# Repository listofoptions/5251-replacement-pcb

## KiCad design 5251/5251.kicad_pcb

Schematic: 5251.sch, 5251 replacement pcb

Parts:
J1: Conn_01x30; BEAMSPRING-CARD-EDGE
U1: F1_SENSE; SENSE_PAD
U2: F1; BEAMSPRING_PAD
U3: F2; BEAMSPRING_PAD
U4: RIGHT_TAB_SENSE; SENSE_PAD
U5: TILDE; BEAMSPRING_PAD
U6: 1; BEAMSPRING_PAD
U7: 2; BEAMSPRING_PAD
U8: 3; BEAMSPRING_PAD
U9: 4; BEAMSPRING_PAD
U10: 5; BEAMSPRING_PAD
U11: 6; BEAMSPRING_PAD
U12: 7; BEAMSPRING_PAD
U13: 8; BEAMSPRING_PAD
U14: 9; BEAMSPRING_PAD
U15: 0; BEAMSPRING_PAD
U16: -_; BEAMSPRING_PAD
U17: =+; BEAMSPRING_PAD
U18: BACKSPACE; BEAMSPRING_PAD
U19: PAD7; BEAMSPRING_PAD
U20: LEFT_TAB; BEAMSPRING_PAD
U21: PAD9; BEAMSPRING_PAD
U22: DUP; BEAMSPRING_PAD
U23: F3_SENSE; SENSE_PAD
U24: F3; BEAMSPRING_PAD
U25: F4; BEAMSPRING_PAD
U26: F9; BEAMSPRING_PAD
U27: CONTROL; BEAMSPRING_PAD
U28: RIGHT_TAB; BEAMSPRING_PAD
U29: Q; BEAMSPRING_PAD
U30: W; BEAMSPRING_PAD
U31: E; BEAMSPRING_PAD
U32: R; BEAMSPRING_PAD
U33: T; BEAMSPRING_PAD
U34: Y; BEAMSPRING_PAD
U35: U; BEAMSPRING_PAD
U36: I; BEAMSPRING_PAD
U37: O; BEAMSPRING_PAD
U38: P; BEAMSPRING_PAD
U39: BANG-CENT; BEAMSPRING_PAD
U40: \\|; BEAMSPRING_PAD
U41: FIELD_EXIT; BEAMSPRING_PAD
U42: PAD4; BEAMSPRING_PAD
U43: PAD8; BEAMSPRING_PAD
U44: PAD6; BEAMSPRING_PAD
U45: FIELD-; BEAMSPRING_PAD
U46: F5_SENSE; SENSE_PAD
U47: F5; BEAMSPRING_PAD
U48: F6; BEAMSPRING_PAD
U49: F9_SENSE; SENSE_PAD
U50: LEFT_SHIFT; BEAMSPRING_PAD
U51: <>; BEAMSPRING_PAD
U52: A; BEAMSPRING_PAD
U53: S; BEAMSPRING_PAD
U54: D; BEAMSPRING_PAD
U55: F; BEAMSPRING_PAD
U56: G; BEAMSPRING_PAD
U57: H; BEAMSPRING_PAD
U58: J; BEAMSPRING_PAD
U59: K; BEAMSPRING_PAD
U60: L; BEAMSPRING_PAD
U61: ;; BEAMSPRING_PAD
U62: '; BEAMSPRING_PAD
U63: {}; BEAMSPRING_PAD
U64: RETURN; BEAMSPRING_PAD
U65: PAD1; BEAMSPRING_PAD
U66: PAD5; BEAMSPRING_PAD
U67: PAD3; BEAMSPRING_PAD
U68: FIELD+; BEAMSPRING_PAD
U69: F7_SENSE; SENSE_PAD
U70: F7; BEAMSPRING_PAD
U71: F8; BEAMSPRING_PAD
U72: F10; BEAMSPRING_PAD
U73: ERROR_RESET_SENSE; SENSE_PAD
U74: ERROR_RESET; BEAMSPRING_PAD
U75: Z; BEAMSPRING_PAD
U76: X; BEAMSPRING_PAD
U77: C; BEAMSPRING_PAD
U78: V; BEAMSPRING_PAD
U79: B; BEAMSPRING_PAD
U80: N; BEAMSPRING_PAD
U81: M; BEAMSPRING_PAD
U82: ,,; BEAMSPRING_PAD
U83: ..; BEAMSPRING_PAD
U84: /; BEAMSPRING_PAD
U85: SPACE; BEAMSPRING_PAD
U86: RIGHT_SHIFT; BEAMSPRING_PAD
U87: ENTER/REC_ADV; BEAMSPRING_PAD
U88: PAD0_SENSE; SENSE_PAD
U89: PAD2; BEAMSPRING_PAD
U90: PAD0; BEAMSPRING_PAD
U91: PAD.; BEAMSPRING_PAD

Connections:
COL0: J1.2, U1.2, U23.2, U46.2, U69.2
COL1: J1.3, U2.2, U24.2, U47.2, U70.2
COL2: J1.4, U3.2, U25.2, U48.2, U71.2
COL3: J1.5, U26.2, U49.2, U72.2
COL4: J1.6, U4.2, U27.2, U50.2, U73.2
COL5: J1.7, U5.2, U28.2, U51.2, U74.2
COL6: J1.8, U6.2, U29.2, U52.2, U75.2
COL7: J1.9, U7.2, U30.2, U53.2, U76.2
COL8: J1.10, U8.2, U31.2, U54.2, U77.2
COL9: J1.11, U9.2, U32.2, U55.2, U78.2
COL10: J1.12, U10.2, U33.2, U56.2, U79.2
COL11: J1.13, U11.2, U34.2, U57.2, U80.2
COL12: J1.14, U12.2, U35.2, U58.2, U81.2
COL13: J1.15, U13.2, U36.2, U59.2, U82.2
COL14: J1.17, U14.2, U37.2, U60.2, U83.2
COL15: J1.18, U15.2, U38.2, U61.2, U84.2
COL16: J1.19, U16.2, U39.2, U62.2, U85.2
COL17: J1.20, U17.2, U40.2, U63.2, U86.2
COL18: J1.21, U18.2, U41.2, U64.2, U87.2
COL19: J1.22, U19.2, U42.2, U65.2, U88.2
COL20: J1.23, U20.2, U43.2, U66.2, U89.2
COL21: J1.24, U21.2, U44.2, U67.2, U90.2
COL22: J1.25, U22.2, U45.2, U68.2, U91.2
GNDA: J1.1, J1.26
ROW0: J1.27, U1.1, U2.1, U3.1, U4.1, U5.1, U6.1, U7.1, U8.1, U9.1, U10.1, U11.1, U12.1, U13.1, U14.1, U15.1, U16.1, U17.1, U18.1, U19.1, U20.1, U21.1, U22.1
ROW1: J1.28, U23.1, U24.1, U25.1, U26.1, U27.1, U28.1, U29.1, U30.1, U31.1, U32.1, U33.1, U34.1, U35.1, U36.1, U37.1, U38.1, U39.1, U40.1, U41.1, U42.1, U43.1, U44.1, U45.1
ROW2: J1.29, U46.1, U47.1, U48.1, U49.1, U50.1, U51.1, U52.1, U53.1, U54.1, U55.1, U56.1, U57.1, U58.1, U59.1, U60.1, U61.1, U62.1, U63.1, U64.1, U65.1, U66.1, U67.1, U68.1
ROW3: J1.30, U69.1, U70.1, U71.1, U72.1, U73.1, U74.1, U75.1, U76.1, U77.1, U78.1, U79.1, U80.1, U81.1, U82.1, U83.1, U84.1, U85.1, U86.1, U87.1, U88.1, U89.1, U90.1, U91.1

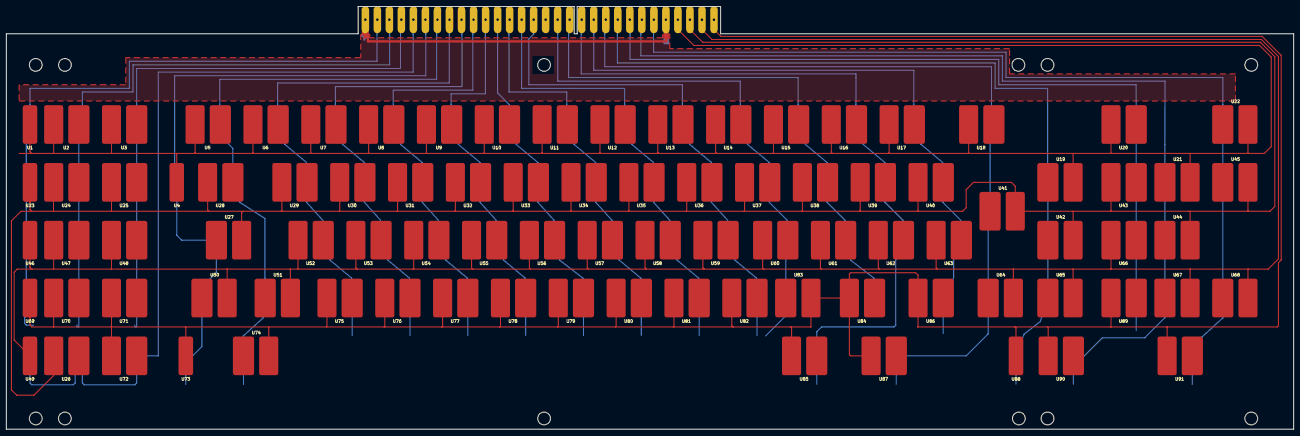
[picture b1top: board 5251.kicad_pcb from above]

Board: 2 copper layers, 424.0 x 139.2 mm, 92 parts (0 on the bottom side), 28 nets.

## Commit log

2020-12-30 inprogress changes made with an alternate backplane
